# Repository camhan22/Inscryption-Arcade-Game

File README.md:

# Inscryption-Arcade-Game
Physical implementation for Inscryption PC game

*Update-06/16/2022
I have created new files for this system. I just need to upload them. 
I created a small PCB to make the electronic cards from the 3rd act that will be placed on board.

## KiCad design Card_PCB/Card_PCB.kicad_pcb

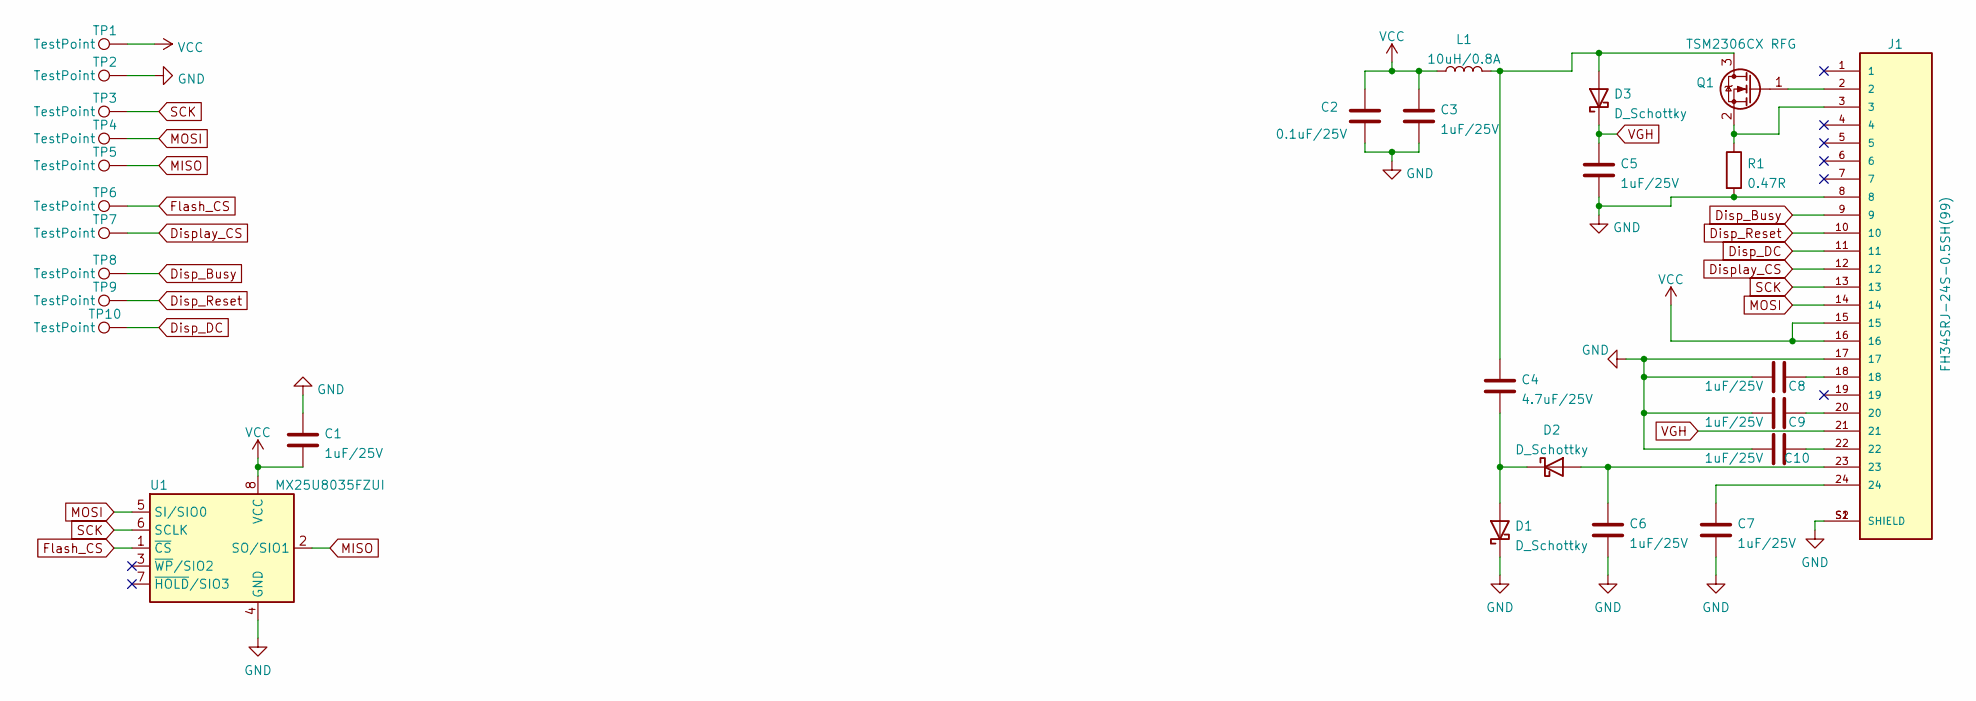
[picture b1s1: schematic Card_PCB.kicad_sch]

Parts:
C1, C3, C5, C6, C7, C8, C9, C10: 1uF/25V; C_0603_1608Metric
C2: 0.1uF/25V; C_0603_1608Metric
C4: 4.7uF/25V; C_0603_1608Metric
D1, D2, D3: D_Schottky; D_SOD-123F
J1: FH34SRJ-24S-0.5SH(99); FH34SRJ_24S; PARTREV NA
L1: 10uH/0.8A; L_Taiyo-Yuden_MD-4040
Q1: TSM2306CX RFG; SOT-23
R1: 0.47R; R_0603_1608Metric
TP1, TP2, TP3, TP4, TP5, TP6, TP7, TP8, TP9, TP10: TestPoint; TestPoint_Pad_2.0x2.0mm
U1: MX25U8035FZUI; SON-8-1EP_3x2mm_P0.5mm_EP1.4x1.6mm

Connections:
Disp_Busy: J1.9, TP8.1
Disp_DC: J1.11, TP10.1
Disp_Reset: J1.10, TP9.1
Display_CS: J1.12, TP7.1
Flash_CS: TP6.1, U1.1 (~CS)
GND: C1.1, C2.1, C3.2, C5.2, C6.2, C7.2, C8.1, C9.1, C10.1, D1.1 (K), J1.8, J1.17, J1.S1 (SHIELD), J1.S2 (SHIELD), R1.2, TP2.1, U1.4 (GND)
MISO: TP5.1, U1.2 (SO/SIO1)
MOSI: J1.14, TP4.1, U1.5 (SI/SIO0)
unnamed: C4.2, D1.2 (A), D2.1 (K)
unnamed: C6.1, D2.2 (A), J1.23
unnamed: C7.1, J1.24
unnamed: C8.2, J1.18
unnamed: C9.2, J1.20
unnamed: C10.2, J1.22
unnamed: C4.1, D3.2 (A), L1.2, Q1.3 (D)
unnamed: J1.2, Q1.1 (G)
unnamed: J1.3, Q1.2 (S), R1.1
SCK: J1.13, TP3.1, U1.6 (SCLK)
VCC: C1.2, C2.2, C3.1, J1.15, J1.16, L1.1, TP1.1, U1.8 (VCC)
VGH: C5.1, D3.1 (K), J1.21

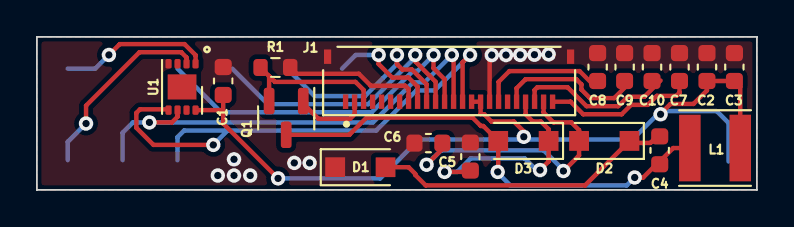
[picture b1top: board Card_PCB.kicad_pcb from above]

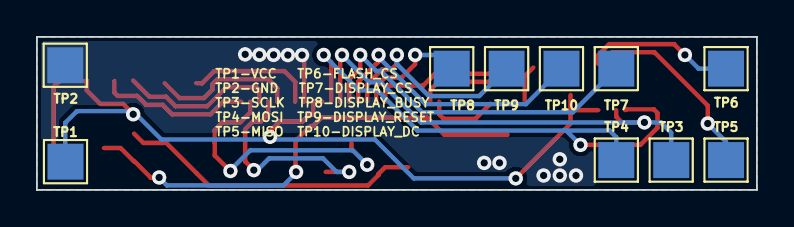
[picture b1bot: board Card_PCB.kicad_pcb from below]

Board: 2 copper layers, 40.0 x 8.5 mm, 28 parts (10 on the bottom side), 20 nets.

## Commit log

2022-01-12 Created parts.txt
    For reference with BOM later
2022-01-12 Updated PCB
2022-01-26 fgvf
2022-01-28 updated schematics and PCB
    Fixed issues between datasheet circuit and my PCB
2022-03-02 new PCB
